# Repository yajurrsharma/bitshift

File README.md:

# BitShift

A fully customisable 60% default mechanical keyboard!

---

## Components
1) Raspberry Pi Pico
2) Click INC OF Linear Switches
3) Plate Mount Stabilizers
4) 1N4148 Diodes
5) QMK Firmware

---

## Links

Onshape Assembly Link - 

https://cad.onshape.com/documents/e934466d28d46fd1f6dcf889/w/7781f521603f614127341e10/e/2dd8a25e8e5661a052460422?renderMode=0&uiState=6ad8b4f65f7c261201e53e1d

### Schematic

---

### PCB

---

### Assembly

---

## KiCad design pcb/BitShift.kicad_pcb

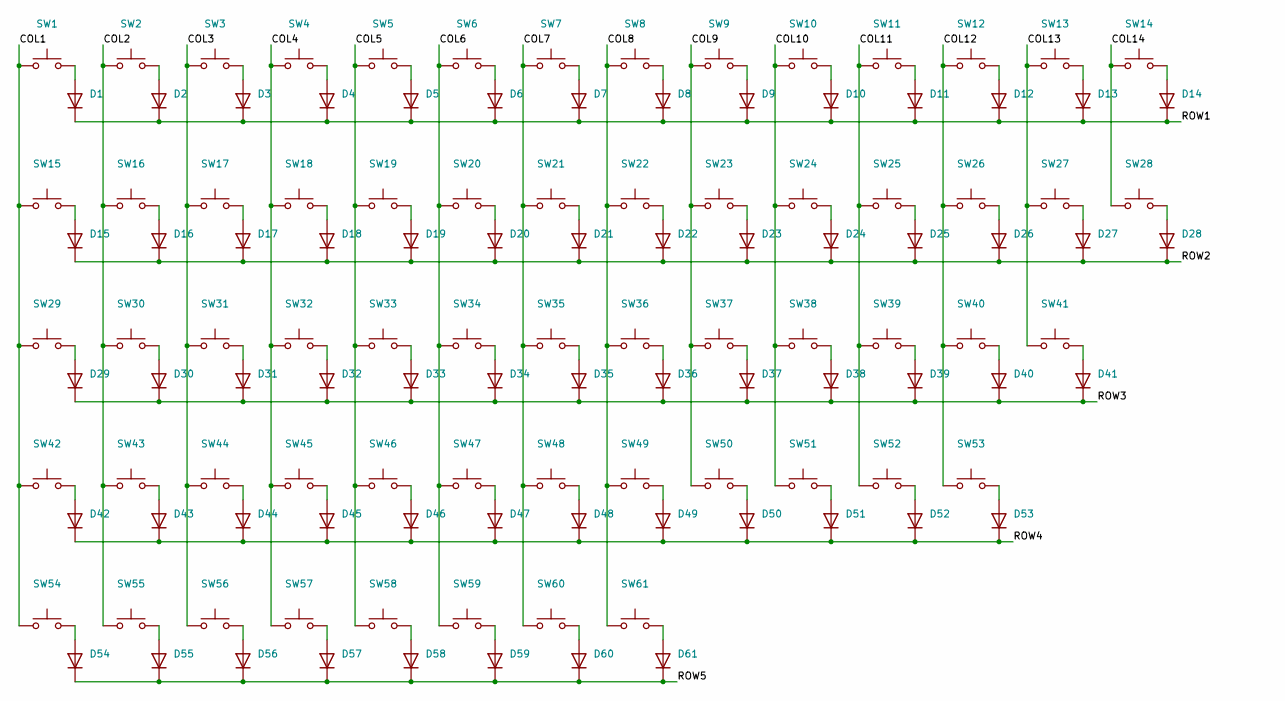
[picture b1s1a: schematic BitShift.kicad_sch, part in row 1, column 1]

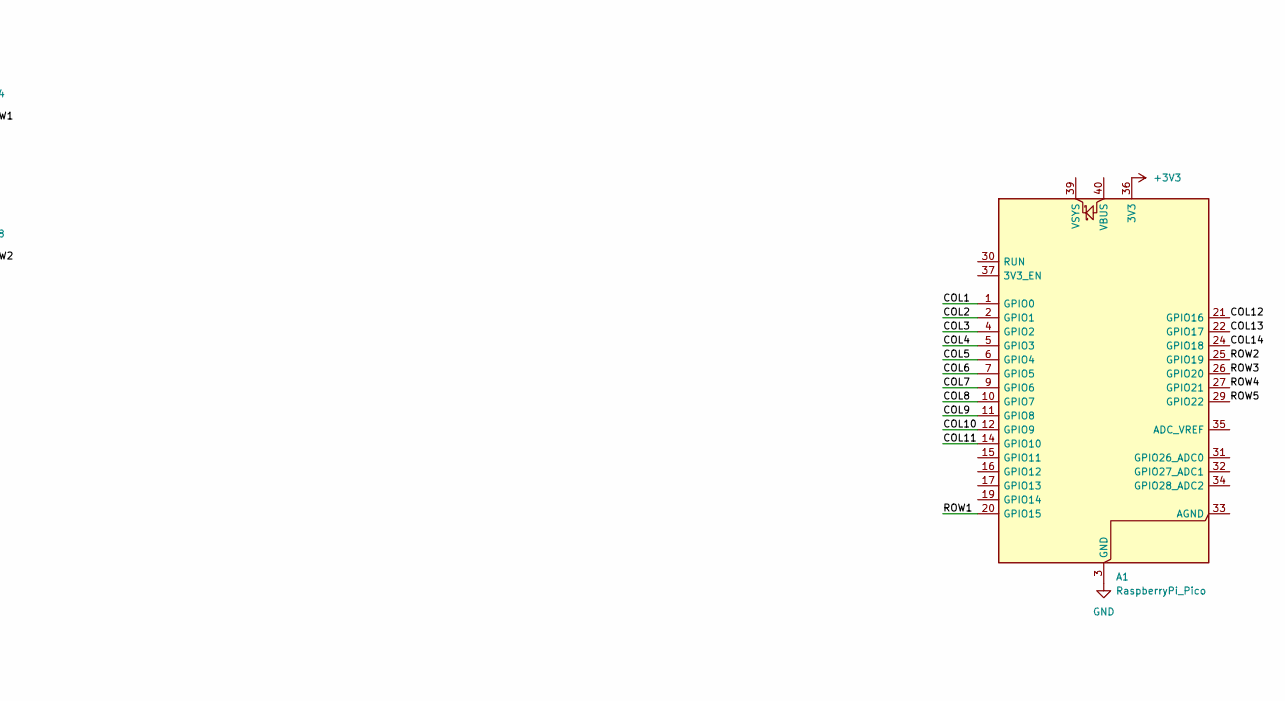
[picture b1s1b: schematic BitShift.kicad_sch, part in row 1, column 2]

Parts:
A1: RaspberryPi_Pico; RaspberryPi_Pico_Common_SMD
D1, D2, D3, D4, D5, D6, D7, D8, D9, D10, D11, D12, D13, D14, D15, D16, D17, D18, D19, D20, D21, D22, D23, D24, D25, D26, D27, D28, D29, D30, D31, D32, D33, D34, D35, D36, D37, D38, D39, D40, D41, D42, D43, D44, D45, D46, D47, D48, D49, D50, D51, D52, D53, D54, D55, D56, D57, D58, D59, D60, D61: 1N4148; D_DO-35_SOD27_P7.62mm_Horizontal
SW1, SW2, SW3, SW4, SW5, SW6, SW7, SW8, SW9, SW10, SW11, SW12, SW13, SW16, SW17, SW18, SW19, SW20, SW21, SW22, SW23, SW24, SW25, SW26, SW27, SW30, SW31, SW32, SW33, SW34, SW35, SW36, SW37, SW38, SW39, SW40, SW43, SW44, SW45, SW46, SW47, SW48, SW49, SW50, SW51, SW52: SW_Push; SW_Cherry_MX_1.00u_Plate
SW14: SW_Push; SW_Cherry_MX_2.00u_Plate
SW15, SW28: SW_Push; SW_Cherry_MX_1.50u_Plate
SW29: SW_Push; SW_Cherry_MX_1.75u_Plate
SW41, SW42: SW_Push; SW_Cherry_MX_2.25u_Plate
SW53: SW_Push; SW_Cherry_MX_2.75u_Plate
SW54, SW55, SW56, SW58, SW59, SW60, SW61: SW_Push; SW_Cherry_MX_1.25u_Plate
SW57: SW_Push; SW_Cherry_MX_6.25u_Plate

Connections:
+3V3: A1.36 (3V3)
/COL1: A1.1 (GPIO0), SW1.1, SW15.1, SW29.1, SW42.1, SW54.1
/COL2: A1.2 (GPIO1), SW2.1, SW16.1, SW30.1, SW43.1, SW55.1
/COL3: A1.4 (GPIO2), SW3.1, SW17.1, SW31.1, SW44.1, SW56.1
/COL4: A1.5 (GPIO3), SW4.1, SW18.1, SW32.1, SW45.1, SW57.1
/COL5: A1.6 (GPIO4), SW5.1, SW19.1, SW33.1, SW46.1, SW58.1
/COL6: A1.7 (GPIO5), SW6.1, SW20.1, SW34.1, SW47.1, SW59.1
/COL7: A1.9 (GPIO6), SW7.1, SW21.1, SW35.1, SW48.1, SW60.1
/COL8: A1.10 (GPIO7), SW8.1, SW22.1, SW36.1, SW49.1, SW61.1
/COL9: A1.11 (GPIO8), SW9.1, SW23.1, SW37.1, SW50.1
/COL10: A1.12 (GPIO9), SW10.1, SW24.1, SW38.1, SW51.1
/COL11: A1.14 (GPIO10), SW11.1, SW25.1, SW39.1, SW52.1
/COL12: A1.21 (GPIO16), SW12.1, SW26.1, SW40.1, SW53.1
/COL13: A1.22 (GPIO17), SW13.1, SW27.1, SW41.1
/COL14: A1.24 (GPIO18), SW14.1, SW28.1
/ROW1: A1.20 (GPIO15), D1.1 (K), D2.1 (K), D3.1 (K), D4.1 (K), D5.1 (K), D6.1 (K), D7.1 (K), D8.1 (K), D9.1 (K), D10.1 (K), D11.1 (K), D12.1 (K), D13.1 (K), D14.1 (K)
/ROW2: A1.25 (GPIO19), D15.1 (K), D16.1 (K), D17.1 (K), D18.1 (K), D19.1 (K), D20.1 (K), D21.1 (K), D22.1 (K), D23.1 (K), D24.1 (K), D25.1 (K), D26.1 (K), D27.1 (K), D28.1 (K)
/ROW3: A1.26 (GPIO20), D29.1 (K), D30.1 (K), D31.1 (K), D32.1 (K), D33.1 (K), D34.1 (K), D35.1 (K), D36.1 (K), D37.1 (K), D38.1 (K), D39.1 (K), D40.1 (K), D41.1 (K)
/ROW4: A1.27 (GPIO21), D42.1 (K), D43.1 (K), D44.1 (K), D45.1 (K), D46.1 (K), D47.1 (K), D48.1 (K), D49.1 (K), D50.1 (K), D51.1 (K), D52.1 (K), D53.1 (K)
/ROW5: A1.29 (GPIO22), D54.1 (K), D55.1 (K), D56.1 (K), D57.1 (K), D58.1 (K), D59.1 (K), D60.1 (K), D61.1 (K)
GND: A1.3 (GND), A1.8 (GND), A1.13 (GND), A1.18 (GND), A1.23 (GND), A1.28 (GND), A1.38 (GND)
unnamed: D1.2 (A), SW1.2
unnamed: D2.2 (A), SW2.2
unnamed: D3.2 (A), SW3.2
unnamed: D4.2 (A), SW4.2
unnamed: D5.2 (A), SW5.2
unnamed: D6.2 (A), SW6.2
unnamed: D7.2 (A), SW7.2
unnamed: D8.2 (A), SW8.2
unnamed: D9.2 (A), SW9.2
unnamed: D10.2 (A), SW10.2
unnamed: D11.2 (A), SW11.2
unnamed: D12.2 (A), SW12.2
unnamed: D13.2 (A), SW13.2
unnamed: D14.2 (A), SW14.2
unnamed: D15.2 (A), SW15.2
unnamed: D16.2 (A), SW16.2
unnamed: D17.2 (A), SW17.2
unnamed: D18.2 (A), SW18.2
unnamed: D19.2 (A), SW19.2
unnamed: D20.2 (A), SW20.2
unnamed: D21.2 (A), SW21.2
unnamed: D22.2 (A), SW22.2
unnamed: D23.2 (A), SW23.2
unnamed: D24.2 (A), SW24.2
unnamed: D25.2 (A), SW25.2
unnamed: D26.2 (A), SW26.2
unnamed: D27.2 (A), SW27.2
unnamed: D28.2 (A), SW28.2
unnamed: D29.2 (A), SW29.2
unnamed: D30.2 (A), SW30.2
unnamed: D31.2 (A), SW31.2
unnamed: D32.2 (A), SW32.2
unnamed: D33.2 (A), SW33.2
unnamed: D34.2 (A), SW34.2
unnamed: D35.2 (A), SW35.2
unnamed: D36.2 (A), SW36.2
unnamed: D37.2 (A), SW37.2
unnamed: D38.2 (A), SW38.2
unnamed: D39.2 (A), SW39.2
unnamed: D40.2 (A), SW40.2
unnamed: D41.2 (A), SW41.2
unnamed: D42.2 (A), SW42.2
unnamed: D43.2 (A), SW43.2
unnamed: D44.2 (A), SW44.2
unnamed: D45.2 (A), SW45.2
unnamed: D46.2 (A), SW46.2
unnamed: D47.2 (A), SW47.2
unnamed: D48.2 (A), SW48.2
unnamed: D49.2 (A), SW49.2
unnamed: D50.2 (A), SW50.2
unnamed: D51.2 (A), SW51.2
unnamed: D52.2 (A), SW52.2
unnamed: D53.2 (A), SW53.2
unnamed: D54.2 (A), SW54.2
unnamed: D55.2 (A), SW55.2
unnamed: D56.2 (A), SW56.2
unnamed: D57.2 (A), SW57.2
unnamed: D58.2 (A), SW58.2
unnamed: D59.2 (A), SW59.2
unnamed: D60.2 (A), SW60.2
unnamed: D61.2 (A), SW61.2

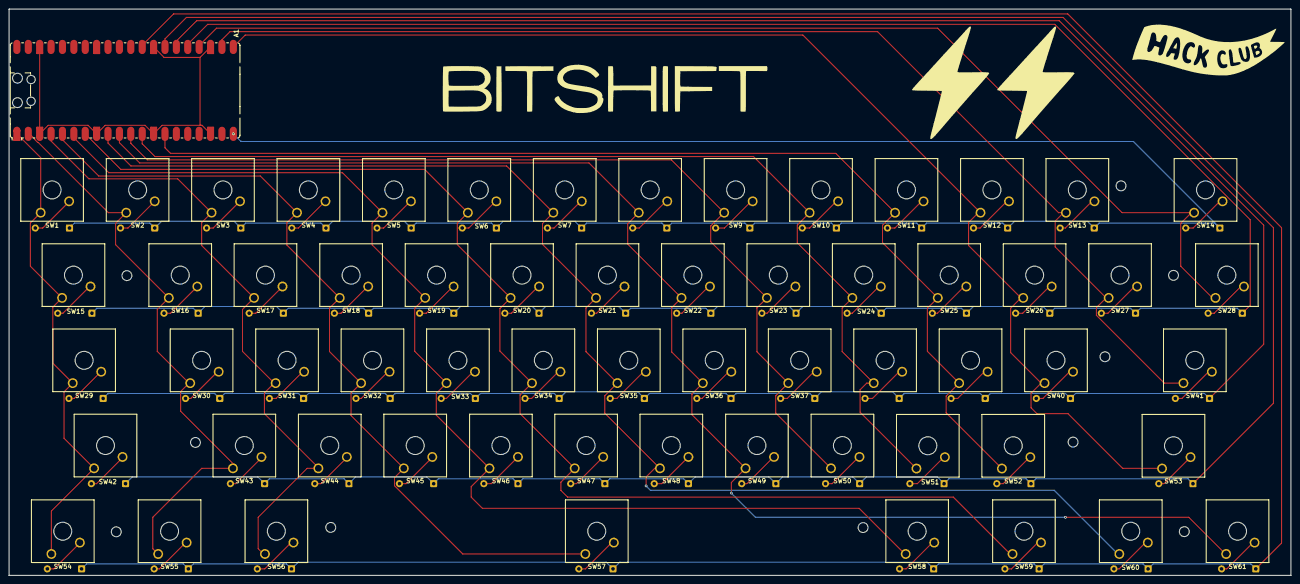
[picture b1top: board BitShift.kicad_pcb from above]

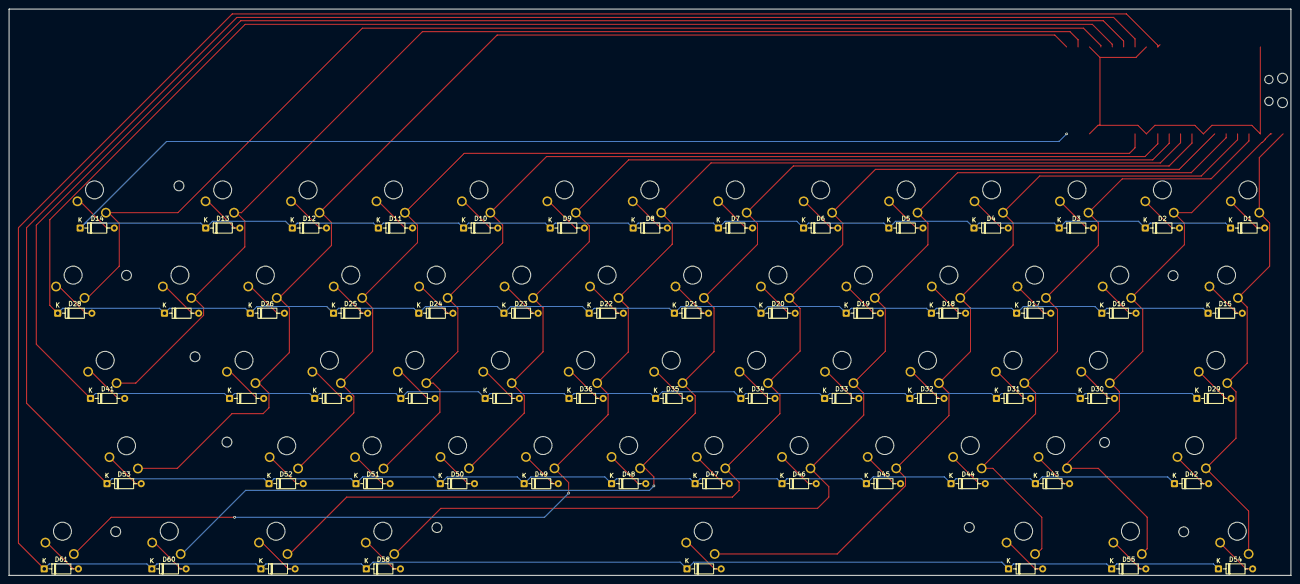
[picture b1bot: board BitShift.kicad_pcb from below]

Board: 2 copper layers, 285.8 x 126.3 mm, 123 parts (61 on the bottom side), 81 nets.
